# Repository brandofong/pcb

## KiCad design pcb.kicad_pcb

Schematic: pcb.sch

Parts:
C1: 10uF; C_0805_2012Metric
C2, C5, C6: 0.1uF; C_0805_2012Metric
C3, C4: 22pF; C_0805_2012Metric
C7: 1uF; C_0805_2012Metric
D1, D2, D3, D4: D_Small; D_SOD-123
F1: 500mA; Fuse_1206_3216Metric
MX1, MX2, MX3, MX4: MX-NoLED; MX-1U-NoLED
R1, R2: 22; R_0805_2012Metric
R3, R4: 10k; R_0805_2012Metric
SW1: SW_Push; SKQG-1155865
U1: ATmega32U4-AU; TQFP-44_10x10mm_P0.8mm
USB1: Molex-0548190589
Y1: 16MHz; Crystal_SMD_3225-4Pin_3.2x2.5mm

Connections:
+5V: C1.1, C2.1, C5.1, C6.1, F1.1, R3.1, U1.2 (UVCC), U1.7 (VBUS), U1.14 (VCC), U1.24 (AVCC), U1.34 (VCC), U1.44 (AVCC)
COL0: MX1.1, MX2.1
COL1: MX3.1, MX4.1
D+: R1.2, USB1.3
D-: R2.2, USB1.4
GND: C1.2, C2.2, C3.2, C4.2, C5.2, C6.2, C7.2, R4.1, SW1.1, U1.5 (UGND), U1.15 (GND), U1.23 (GND), U1.35 (GND), U1.43 (GND), USB1.1, Y1.2, Y1.4
unnamed: C3.1, U1.17 (XTAL1), Y1.1
unnamed: C4.1, U1.16 (XTAL2), Y1.3
unnamed: C7.1, U1.6 (UCAP)
unnamed: D1.2, MX1.2
unnamed: D2.2, MX2.2
unnamed: D3.2, MX3.2
unnamed: D4.2, MX4.2
unnamed: R1.1, U1.4 (D+)
unnamed: R2.1, U1.3 (D-)
unnamed: R3.2, SW1.2, U1.13 (~RESET)
unnamed: R4.2, U1.33 (~HWB~/PE2)
ROW0: D1.1, D3.1
ROW1: D2.1, D4.1
VCC: F1.2, USB1.5

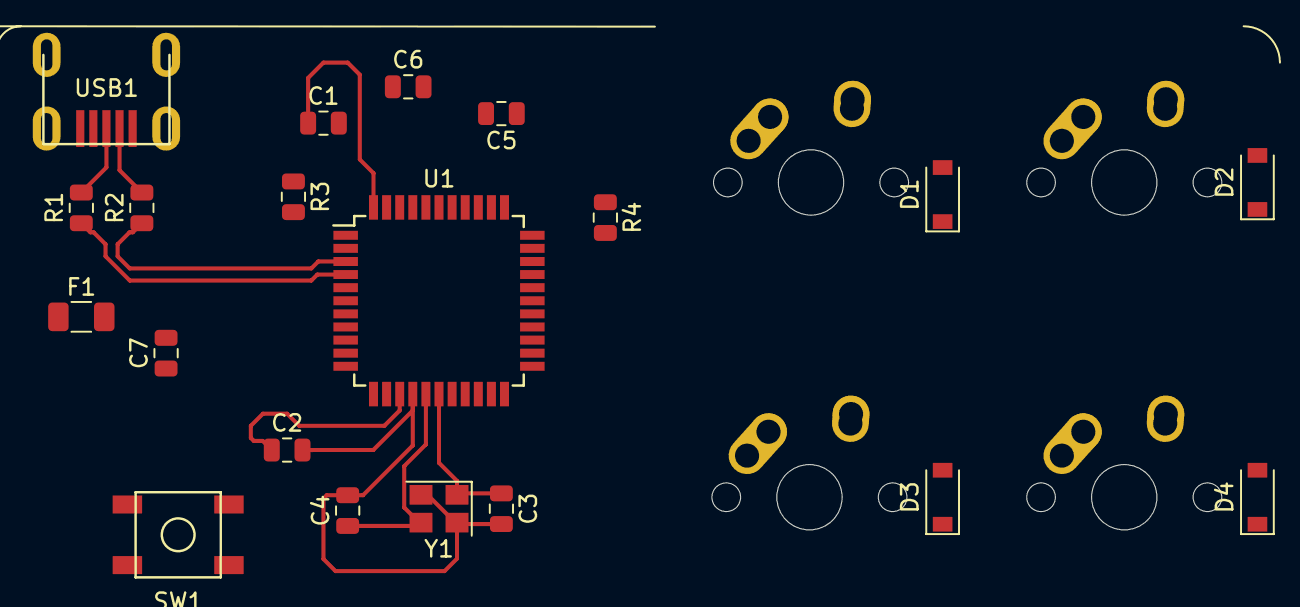
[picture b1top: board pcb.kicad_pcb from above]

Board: 2 copper layers, 24 parts (0 on the bottom side), 20 nets.

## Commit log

2026-01-04 init
2026-01-04 Add submodules
2026-01-04 init2
2026-01-04 left done
2026-01-04 most done
2026-01-04 schematic started
2026-01-04 final
2026-01-04 Update fp-info-cache
